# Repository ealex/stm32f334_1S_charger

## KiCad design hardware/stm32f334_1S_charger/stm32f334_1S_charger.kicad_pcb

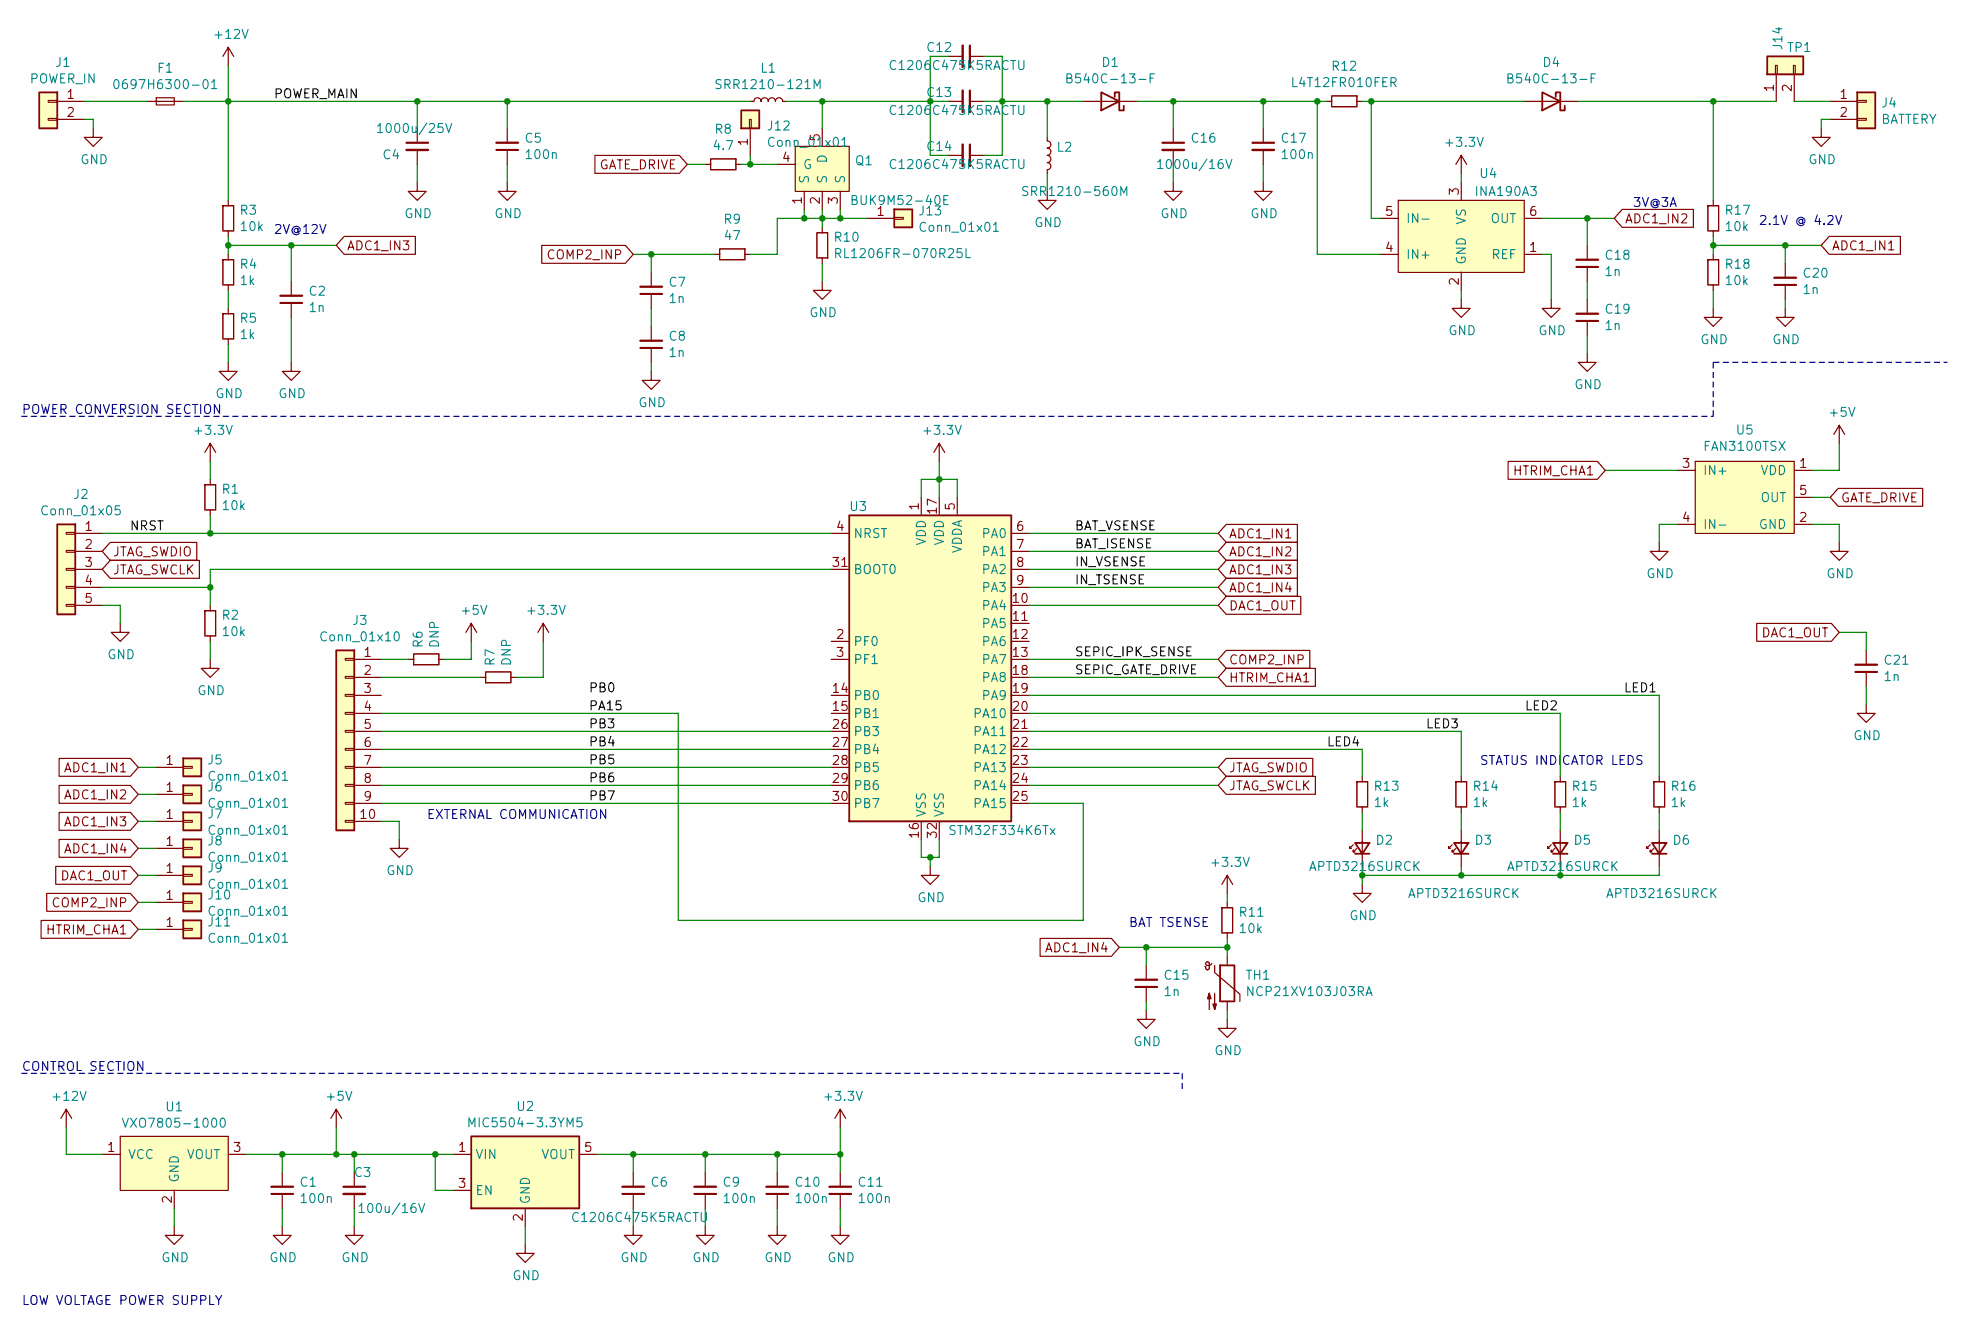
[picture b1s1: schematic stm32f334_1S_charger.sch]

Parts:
C1, C5, C9, C10, C11, C17: 100n; C_1206_3216Metric_Pad1.42x1.75mm_HandSolder
C2, C7, C8, C15, C18, C19, C20, C21: 1n; C_1206_3216Metric_Pad1.42x1.75mm_HandSolder
C3: 100u/16V; CP_Radial_D6.3mm_P2.50mm
C4: 1000u/25V; CP_Radial_D13.0mm_P5.00mm
C6, C12, C13, C14: C1206C475K5RACTU; C_1206_3216Metric_Pad1.42x1.75mm_HandSolder
C16: 1000u/16V; CP_Radial_D10.0mm_P5.00mm
D1, D4: B540C-13-F; D_SMC_Handsoldering
D2, D3, D5, D6: APTD3216SURCK; LED_1206_3216Metric
F1: 0697H6300-01
J1: POWER_IN; PinHeader_1x02_P2.54mm_Vertical
J2: Conn_01x05; PinHeader_1x05_P2.54mm_Vertical
J3: Conn_01x10; PinHeader_1x10_P2.54mm_Vertical
J4: BATTERY; 18650_holder
J5, J6, J7, J8, J9, J10, J11, J12, J13: Conn_01x01; PinHeader_1x01_P2.54mm_Vertical
J14: TP1; PinHeader_1x02_P2.54mm_Vertical
L1: SRR1210-121M; L_Bourns_SRR1210A
L2: SRR1210-560M; L_Bourns_SRR1210A
Q1: BUK9M52-40E; LFPAK33
R1, R2, R3, R11, R17, R18: 10k; R_1206_3216Metric_Pad1.42x1.75mm_HandSolder
R4, R5, R13, R14, R15, R16: 1k; R_1206_3216Metric_Pad1.42x1.75mm_HandSolder
R6, R7: DNP; R_1206_3216Metric_Pad1.42x1.75mm_HandSolder
R8: 4.7; R_1206_3216Metric_Pad1.42x1.75mm_HandSolder
R9: 47; R_1206_3216Metric_Pad1.42x1.75mm_HandSolder
R10: RL1206FR-070R25L; R_1206_3216Metric_Pad1.42x1.75mm_HandSolder
R12: L4T12FR010FER; R_1206_3216Metric_Pad1.42x1.75mm_HandSolder
TH1: NCP21XV103J03RA; R_0805_2012Metric_Pad1.15x1.40mm_HandSolder
U1: VXO7805-1000
U2: MIC5504-3.3YM5; SOT-23-5
U3: STM32F334K6Tx; LQFP-32_7x7mm_P0.8mm
U4: INA190A3; SC70-6
U5: FAN3100TSX; SOT-23-5_HandSoldering

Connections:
+3V3: C6.2, C9.2, C10.2, C11.2, R1.1, R7.2, R11.1, U2.5 (VOUT), U3.1 (VDD), U3.5 (VDDA), U3.17 (VDD), U4.3 (VS)
+5V: C1.2, C3.1, R6.2, U1.3 (VOUT), U2.1 (VIN), U2.3 (EN), U5.1 (VDD)
+12V: C4.1, C5.2, F1.2, L1.1, R3.1, U1.1 (VCC)
/LED1: R16.1, U3.19 (PA9)
/LED2: R15.1, U3.20 (PA10)
/LED3: R14.1, U3.21 (PA11)
/LED4: R13.1, U3.22 (PA12)
/NRST: J2.1, R1.2, U3.4 (NRST)
/PA15: J3.4, U3.25 (PA15)
/PB3: J3.5, U3.26 (PB3)
/PB4: J3.6, U3.27 (PB4)
/PB5: J3.7, U3.28 (PB5)
/PB6: J3.8, U3.29 (PB6)
/PB7: J3.9, U3.30 (PB7)
ADC1_IN1: C20.2, J5.1, R17.2, R18.1, U3.6 (PA0)
ADC1_IN2: C18.2, J6.1, U3.7 (PA1), U4.6 (OUT)
ADC1_IN3: C2.2, J7.1, R3.2, R4.1, U3.8 (PA2)
ADC1_IN4: C15.2, J8.1, R11.2, TH1.1, U3.9 (PA3)
COMP2_INP: C7.2, J10.1, R9.2, U3.13 (PA7)
DAC1_OUT: C21.2, J9.1, U3.10 (PA4)
GATE_DRIVE: R8.2, U5.5 (OUT)
GND: C1.1, C2.1, C3.2, C4.2, C5.1, C6.1, C8.1, C9.1, C10.1, C11.1, C15.1, C16.2, C17.2, C19.1, C20.1, C21.1, D2.1 (K), D3.1 (K), D5.1 (K), D6.1 (K), J1.2, J2.5, J3.10, J4.2, L2.2, R2.2, R5.2, R10.1, R18.2, TH1.2, U1.2 (GND), U2.2 (GND), U3.16 (VSS), U3.32 (VSS), U4.1 (REF), U4.2 (GND), U5.2 (GND), U5.4 (IN-)
HTRIM_CHA1: J11.1, U3.18 (PA8), U5.3 (IN+)
JTAG_SWCLK: J2.3, U3.24 (PA14)
JTAG_SWDIO: J2.2, U3.23 (PA13)
unnamed: C7.1, C8.2
unnamed: C12.1, C13.1, C14.1, D1.2 (A), L2.1
unnamed: C12.2, C13.2, C14.2, L1.2, Q1.5 (D)
unnamed: C16.1, C17.1, D1.1 (K), R12.2, U4.4 (IN+)
unnamed: C18.1, C19.2
unnamed: D2.2 (A), R13.2
unnamed: D3.2 (A), R14.2
unnamed: D4.1 (K), J14.1, R17.1
unnamed: D4.2 (A), R12.1, U4.5 (IN-)
unnamed: D5.2 (A), R15.2
unnamed: D6.2 (A), R16.2
unnamed: F1.1, J1.1
unnamed: J2.4, R2.1, U3.31 (BOOT0)
unnamed: J3.1, R6.1
unnamed: J3.2, R7.1
unnamed: J12.1, Q1.4 (G), R8.1
unnamed: J13.1, Q1.1 (S), Q1.2 (S), Q1.3 (S), R9.1, R10.2
unnamed: J4.1, J14.2
unnamed: R4.2, R5.1

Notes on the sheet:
2V@12V
2.1V @ 4.2V
3V@3A
POWER CONVERSION SECTION
LOW VOLTAGE POWER SUPPLY
CONTROL SECTION
STATUS INDICATOR LEDS
EXTERNAL COMMUNICATION
BAT TSENSE

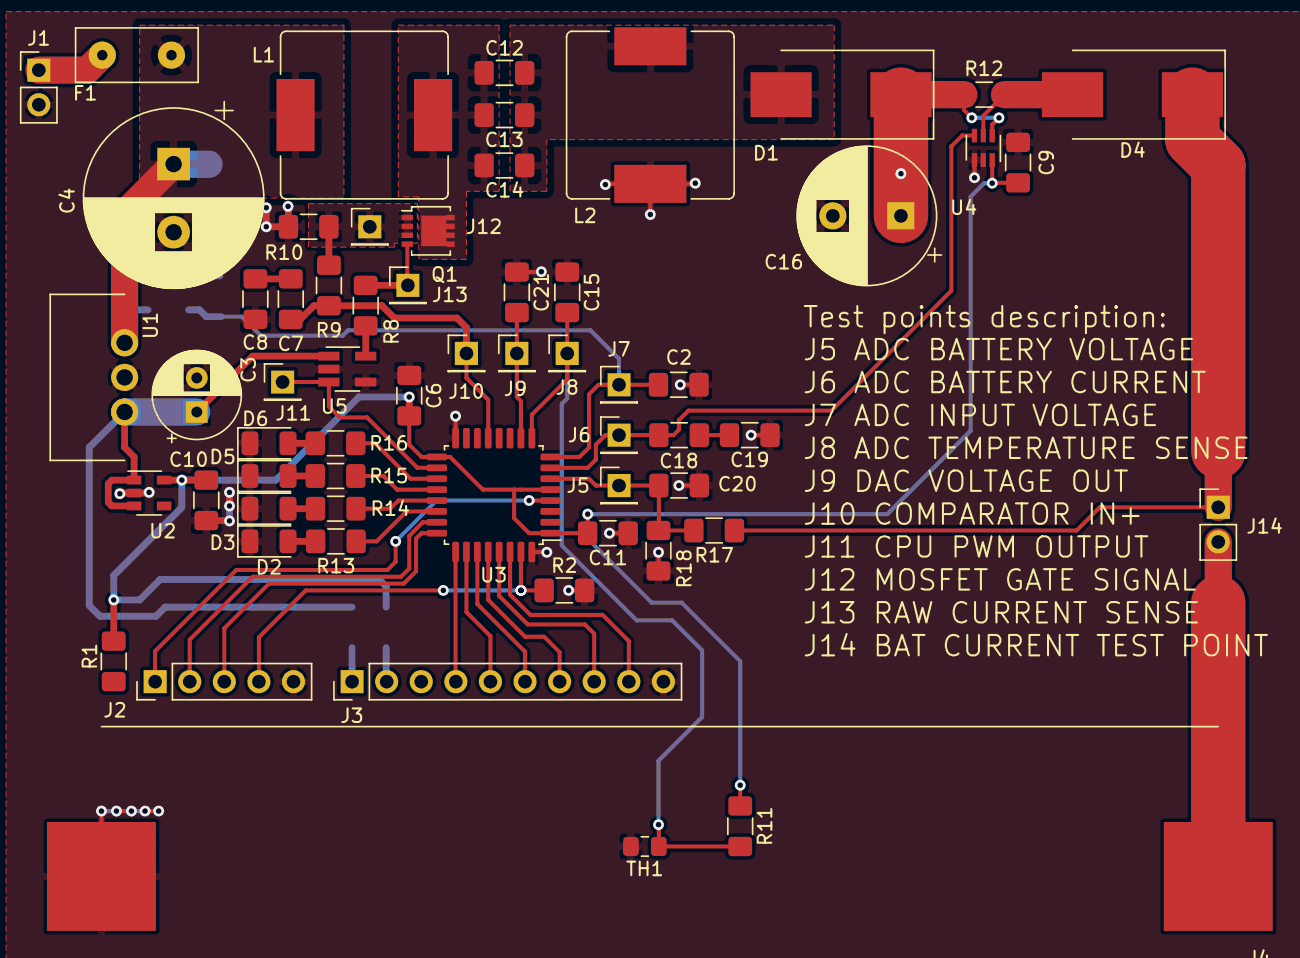
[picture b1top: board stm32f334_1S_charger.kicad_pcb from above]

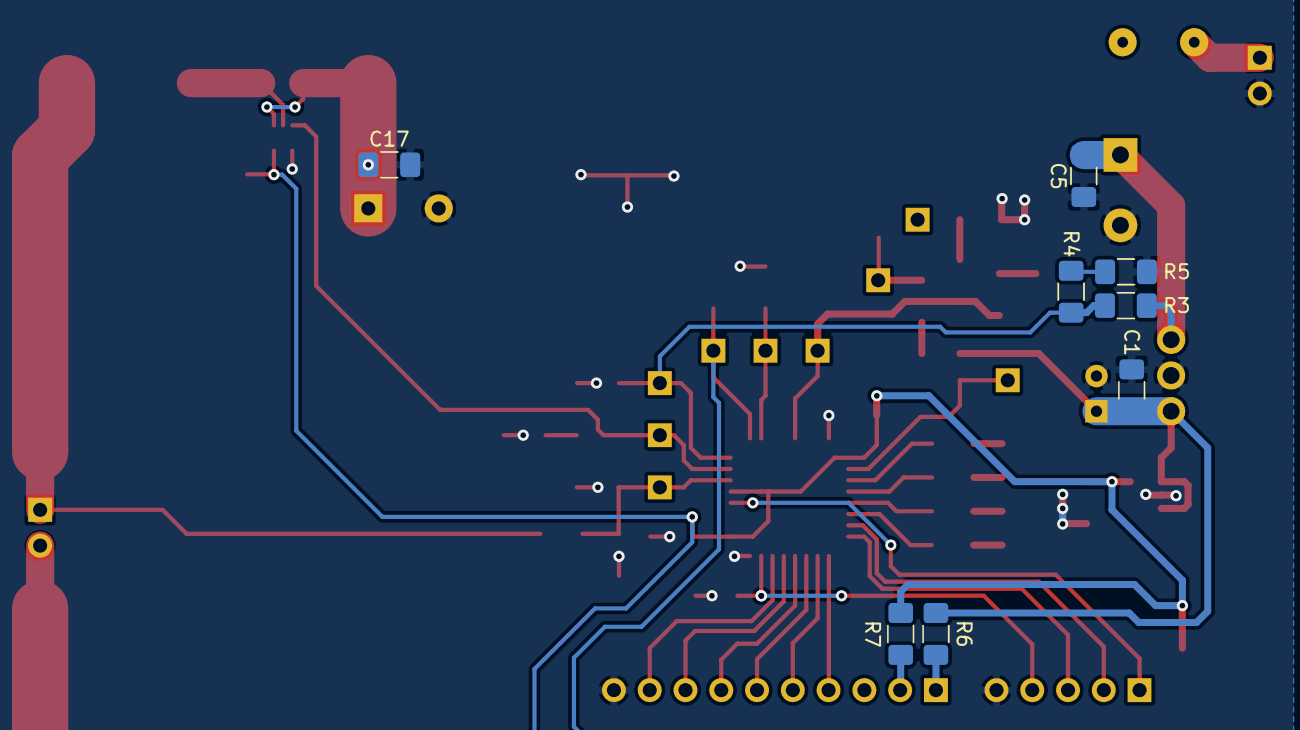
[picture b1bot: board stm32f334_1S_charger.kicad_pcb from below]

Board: 2 copper layers, 69 parts (8 on the bottom side), 44 nets.

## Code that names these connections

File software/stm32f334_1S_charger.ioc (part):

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Mcu.Name=STM32F334K(4-6-8)Tx
Mcu.Package=LQFP32
Mcu.UserName=STM32F334K6Tx
PA0.Mode=IN1-Single-Ended
PA0.Signal=ADC1_IN1
PA1.Mode=IN2-Single-Ended
PA1.Signal=ADC1_IN2
PA10.GPIOParameters=GPIO_Label
PA10.GPIO_Label=LED2
PA10.Signal=GPIO_Output
PA11.GPIOParameters=GPIO_Label
PA11.GPIO_Label=LED3
PA11.Signal=GPIO_Output
PA12.GPIOParameters=GPIO_Label
PA12.GPIO_Label=LED4
PA12.Signal=GPIO_Output
PA13.Mode=Serial_Wire
PA13.Signal=SYS_JTMS-SWDIO
PA14.Mode=Serial_Wire
PA14.Signal=SYS_JTCK-SWCLK
PA2.Mode=IN3-Single-Ended
PA2.Signal=ADC1_IN3
PA3.Mode=IN4-Single-Ended
PA3.Signal=ADC1_IN4
PA4.Signal=SharedAnalog_PA4
PA7.Mode=INP
PA7.Signal=COMP2_INP
PA8.Mode=Output_TA1
PA8.Signal=HRTIM1_CHA1
PA9.GPIOParameters=GPIO_Label
PA9.GPIO_Label=LED1
PA9.Signal=GPIO_Output
RCC.HSEPLLFreq_Value=8000000
RCC.HSE_VALUE=8000000
RCC.SYSCLKFreq_VALUE=64000000
RCC.SYSCLKSourceVirtual=RCC_SYSCLKSOURCE_PLLCLK
board=custom

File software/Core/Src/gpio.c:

/**
  ******************************************************************************
  * File Name          : gpio.c
  * Description        : This file provides code for the configuration
  *                      of all used GPIO pins.
  ******************************************************************************
  * @attention
  *
  * <h2><center>&copy; Copyright (c) 2020 STMicroelectronics.
  * All rights reserved.</center></h2>
  *
  * This software component is licensed by ST under BSD 3-Clause license,
  * the "License"; You may not use this file except in compliance with the
  * License. You may obtain a copy of the License at:
  *                        opensource.org/licenses/BSD-3-Clause
  *
  ******************************************************************************
  */

/* Includes ------------------------------------------------------------------*/
#include "gpio.h"
/* USER CODE BEGIN 0 */

/* USER CODE END 0 */

/*----------------------------------------------------------------------------*/
/* Configure GPIO                                                             */
/*----------------------------------------------------------------------------*/
/* USER CODE BEGIN 1 */

/* USER CODE END 1 */

/** Configure pins as 
        * Analog 
        * Input 
        * Output
        * EVENT_OUT
        * EXTI
        * Free pins are configured automatically as Analog (this feature is enabled through 
        * the Code Generation settings)
*/
void MX_GPIO_Init(void)
{

  GPIO_InitTypeDef GPIO_InitStruct = {0};

  /* GPIO Ports Clock Enable */
  __HAL_RCC_GPIOF_CLK_ENABLE();
  __HAL_RCC_GPIOA_CLK_ENABLE();
  __HAL_RCC_GPIOB_CLK_ENABLE();

  /*Configure GPIO pin Output Level */
  HAL_GPIO_WritePin(GPIOA, LED1_Pin|LED2_Pin|LED3_Pin|LED4_Pin, GPIO_PIN_RESET);

  /*Configure GPIO pins : PF0 PF1 */
  GPIO_InitStruct.Pin = GPIO_PIN_0|GPIO_PIN_1;
  GPIO_InitStruct.Mode = GPIO_MODE_ANALOG;
  GPIO_InitStruct.Pull = GPIO_NOPULL;
  HAL_GPIO_Init(GPIOF, &GPIO_InitStruct);

  /*Configure GPIO pins : PA5 PA6 PA15 */
  GPIO_InitStruct.Pin = GPIO_PIN_5|GPIO_PIN_6|GPIO_PIN_15;
  GPIO_InitStruct.Mode = GPIO_MODE_ANALOG;
  GPIO_InitStruct.Pull = GPIO_NOPULL;
  HAL_GPIO_Init(GPIOA, &GPIO_InitStruct);

  /*Configure GPIO pins : PB0 PB1 PB3 PB4 
                           PB5 PB6 PB7 */
  GPIO_InitStruct.Pin = GPIO_PIN_0|GPIO_PIN_1|GPIO_PIN_3|GPIO_PIN_4 
                          |GPIO_PIN_5|GPIO_PIN_6|GPIO_PIN_7;
  GPIO_InitStruct.Mode = GPIO_MODE_ANALOG;
  GPIO_InitStruct.Pull = GPIO_NOPULL;
  HAL_GPIO_Init(GPIOB, &GPIO_InitStruct);

  /*Configure GPIO pins : PAPin PAPin PAPin PAPin */
  GPIO_InitStruct.Pin = LED1_Pin|LED2_Pin|LED3_Pin|LED4_Pin;
  GPIO_InitStruct.Mode = GPIO_MODE_OUTPUT_PP;
  GPIO_InitStruct.Pull = GPIO_NOPULL;
  GPIO_InitStruct.Speed = GPIO_SPEED_FREQ_LOW;
  HAL_GPIO_Init(GPIOA, &GPIO_InitStruct);

}

/* USER CODE BEGIN 2 */

/* USER CODE END 2 */

/************************ (C) COPYRIGHT STMicroelectronics *****END OF FILE****/

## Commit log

2020-05-24 add docs and schematic
2020-05-26 schematic revision 1 - all parts and footprint + software frame-work
2020-05-27 v1.0 board, pre-production
2020-05-28 v 1.0 board, pre-production
2020-06-14 add bom
